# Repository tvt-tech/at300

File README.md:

# AT300 serial control tool for RP2040 (Micropython)

## Flashing (using [uv](https://docs.astral.sh/uv/getting-started/))
```shell
git clone https://github.com/tvt-tech/at300
cd at300
uv run -s flash.py -p /dev/ttyUSB0 -b 115200
```

## Upgrade
```shell
git pull
uv run -s flash.py -p /dev/ttyUSB0 -b 115200
```

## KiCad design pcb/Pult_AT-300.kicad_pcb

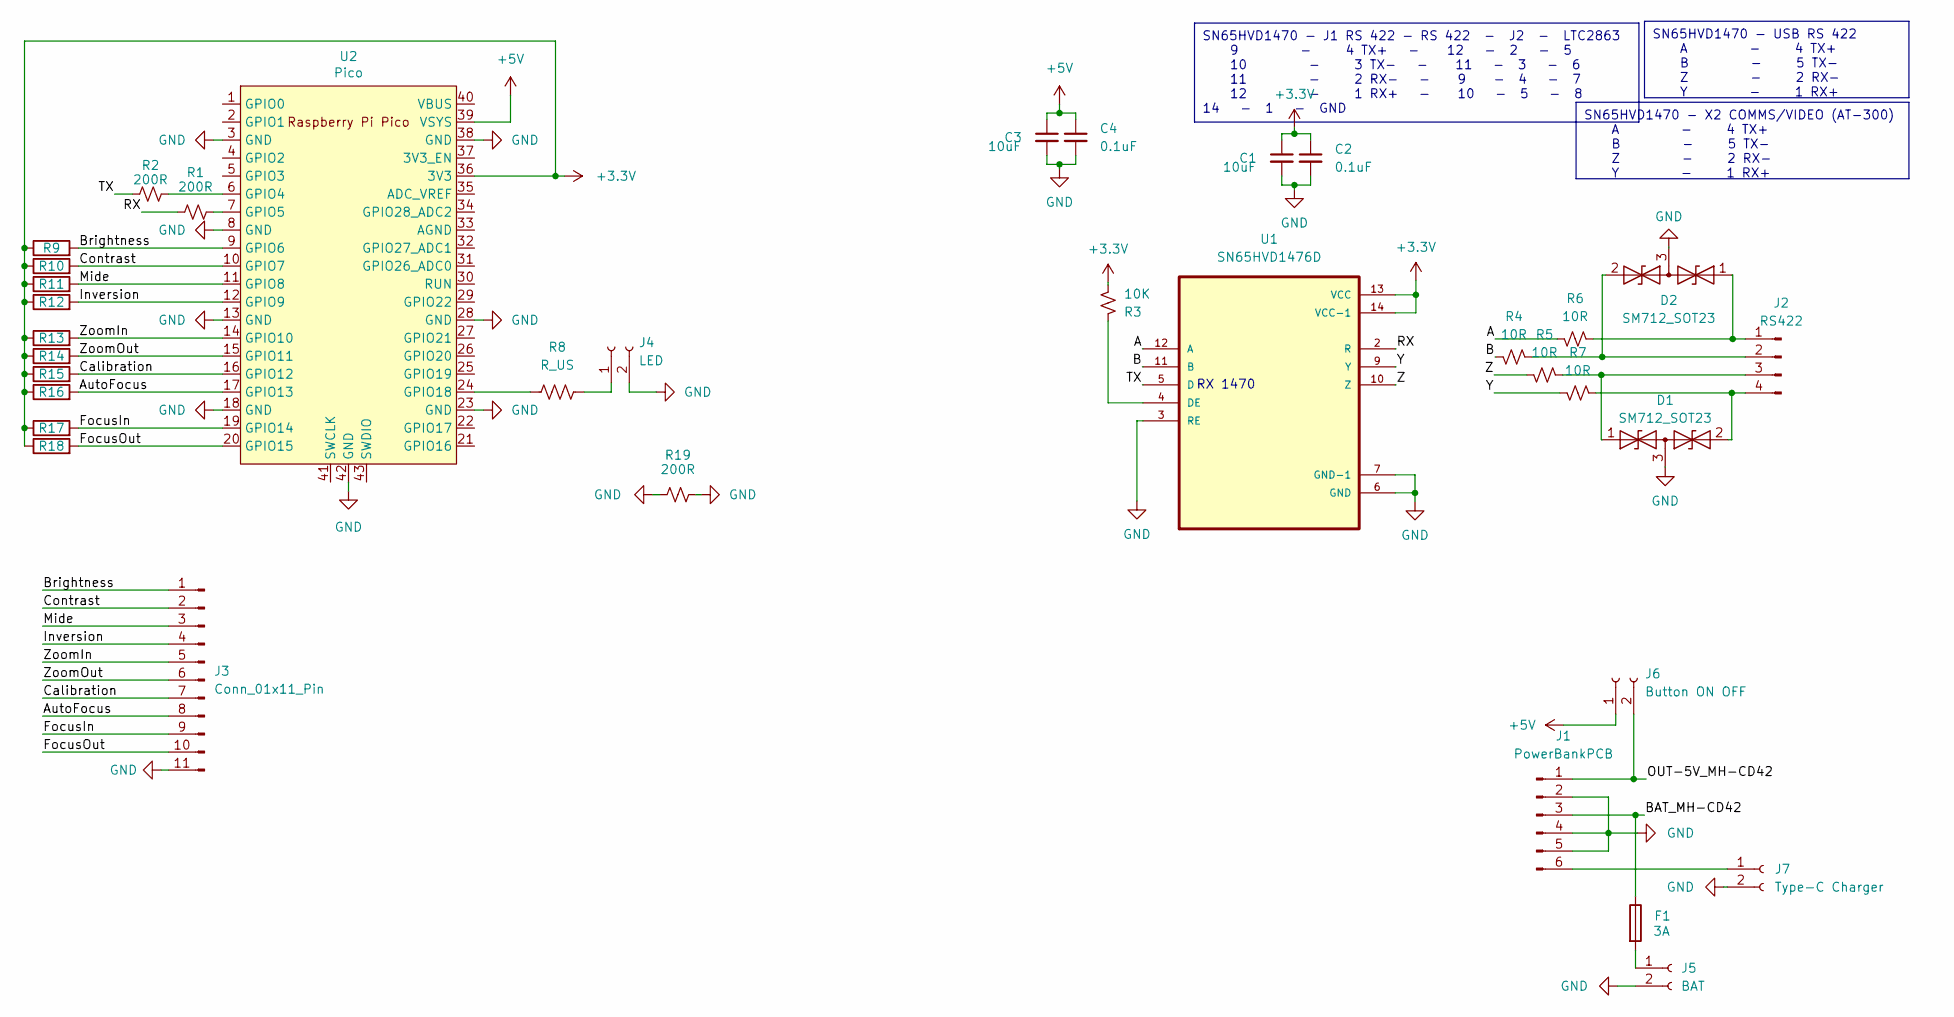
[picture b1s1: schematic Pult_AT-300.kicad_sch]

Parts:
C1, C3: 10uF; C_1206_3216Metric
C2, C4: 0.1uF; C_0603_1608Metric
D1, D2: SM712_SOT23; SOT-23
F1: 3А; R_1812_4532Metric
J1: PowerBankPCB; PinHeader_1x06_P2.54mm_Vertical
J2: RS422; PinSocket_1x04_P2.54mm_Vertical
J3: Conn_01x11_Pin; PinHeader_1x11_P2.54mm_Vertical
J4: LED; PinHeader_1x02_P2.54mm_Vertical
J5: BAT; PinHeader_1x02_P2.54mm_Vertical
J6: Button ON OFF; TerminalBlock_MetzConnect_Type011_RT05502HBWC_1x02_P5.00mm_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
J7: Type-C Charger; PinHeader_1x02_P2.54mm_Vertical
R1, R2: 200R; R_0603_1608Metric
R3: 10K; R_0603_1608Metric
R4, R5, R6, R7: 10R; R_0603_1608Metric
R8: R_US; R_0603_1608Metric
R9, R10, R11, R12, R13, R14, R15, R16, R17, R18: R; R_0603_1608Metric
R19: 200R; R_1206_3216Metric
U1: SN65HVD1476D; SOIC-14_3.9x8.7mm_P1.27mm
U2: Pico; RPi_Pico_SMD_TH

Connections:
+3.3V: C1.1, C2.1, R3.1, R9.1, R10.1, R11.1, R12.1, R13.1, R14.1, R15.1, R16.1, R17.1, R18.1, U1.13 (VCC), U1.14 (VCC-1), U2.36 (3V3)
+5V: C3.1, C4.1, J6.1, U2.39 (VSYS)
/A: R6.2, U1.12 (A)
/AutoFocus: J3.8, R16.2, U2.17 (GPIO13)
/B: R4.2, U1.11 (B)
/BAT_MH-CD42: F1.1, J1.3
/Brightness: J3.1, R9.2, U2.9 (GPIO6)
/Calibration: J3.7, R15.2, U2.16 (GPIO12)
/Contrast: J3.2, R10.2, U2.10 (GPIO7)
/FocusIn: J3.9, R17.2, U2.19 (GPIO14)
/FocusOut: J3.10, R18.2, U2.20 (GPIO15)
/Inversion: J3.4, R12.2, U2.12 (GPIO9)
/Mide: J3.3, R11.2, U2.11 (GPIO8)
/OUT-5V_MH-CD42: J1.1, J6.2
/RX: R1.1, U1.2 (R)
/TX: R2.1, U1.5 (D)
/Y: R7.2, U1.9 (Y)
/Z: R5.2, U1.10 (Z)
/ZoomIn: J3.5, R13.2, U2.14 (GPIO10)
/ZoomOut: J3.6, R14.2, U2.15 (GPIO11)
GND: C1.2, C2.2, C3.2, C4.2, D1.3 (common), D2.3 (common), J1.2, J1.4, J1.5, J3.11, J4.2, J5.2, J7.2, R19.1, R19.2, U1.3 (RE), U1.6 (GND), U1.7 (GND-1), U2.3 (GND), U2.8 (GND), U2.13 (GND), U2.18 (GND), U2.23 (GND), U2.28 (GND), U2.38 (GND), U2.42 (GND)
unnamed: D1.1 (A1), J2.3, R5.1
unnamed: D1.2 (A2), J2.4, R7.1
unnamed: D2.1 (A1), J2.1, R6.1
unnamed: D2.2 (A2), J2.2, R4.1
unnamed: J1.6, J7.1
unnamed: J4.1, R8.2
unnamed: F1.2, J5.1
unnamed: R3.2, U1.4 (DE)
unnamed: R2.2, U2.6 (GPIO4)
unnamed: R1.2, U2.7 (GPIO5)
unnamed: R8.1, U2.24 (GPIO18)

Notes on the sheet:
SN65HVD1470 - J1 RS 422 - RS 422 - J2 - LTC2863 9 - 4 TX+ - 12 - 2 - 5 10 - 3 TX- - 11 - 3 - 6 11 - 2 RX- - 9 - 4 - 7 12 - 1 RX+ - 10 - 5 - 8 14 - 1 - GND
SN65HVD1470 - X2 COMMS/VIDEO (AT-300) A - 4 TX+ B - 5 TX- Z - 2 RX- Y - 1 RX+
SN65HVD1470 - USB RS 422 A - 4 TX+ B - 5 TX- Z - 2 RX- Y - 1 RX+
RX 1470

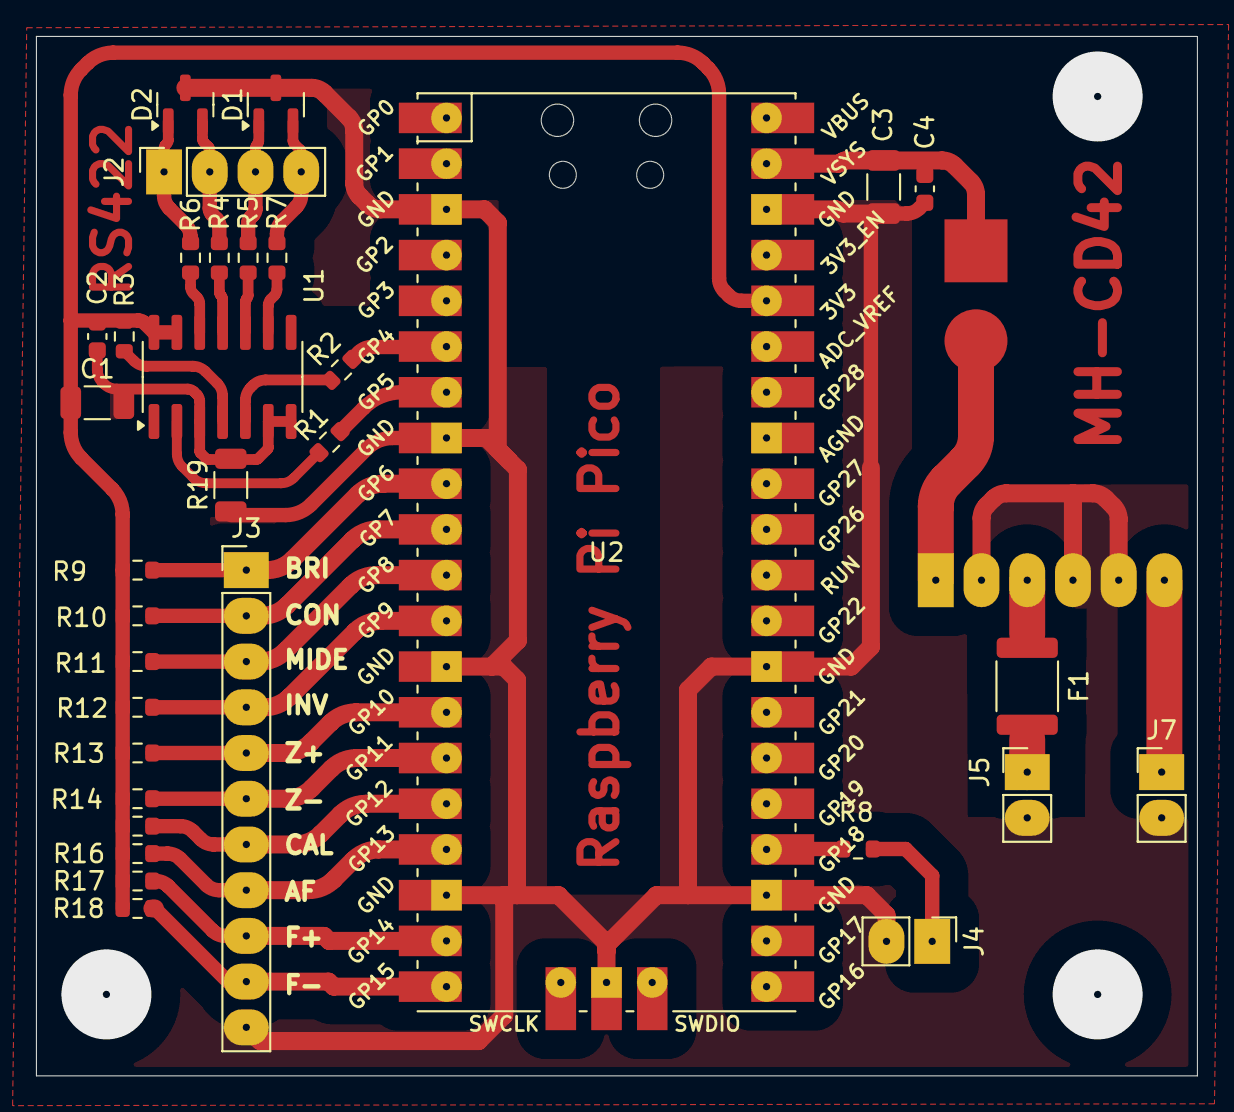
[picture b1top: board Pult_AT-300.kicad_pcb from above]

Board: 2 copper layers, 64.5 x 57.7 mm, 35 parts (1 on the bottom side), 32 nets.

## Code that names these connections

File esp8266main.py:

import time

from machine import UART, Pin

import api

LED = Pin(25, Pin.OUT)

uart = UART(1, baudrate=115200, stop=2)
# RS422Pin = Pin(2, Pin.OUT)
# RS422Pin.on()


class Status:
    Brightness = len(api.CONTRAST) - 1
    Contrast = len(api.BRIGHTNESS) - 1
    Mide = len(api.MIDE) - 1
    Zoom = len(api.Zoom) - 1
    Inversion = api.WhiteHot


# class Button:
#     Brightness = Pin(6, Pin.IN, Pin.PULL_UP)
#     Contrast = Pin(7, Pin.IN, Pin.PULL_UP)
#     Mide = Pin(8, Pin.IN, Pin.PULL_UP)
#     Inversion = Pin(9, Pin.IN, Pin.PULL_UP)
#
#     ZoomIn = Pin(10, Pin.IN, Pin.PULL_UP)
#     ZoomOut = Pin(11, Pin.IN, Pin.PULL_UP)
#     Calibration = Pin(12, Pin.IN, Pin.PULL_UP)
#     AutoFocus = Pin(13, Pin.IN, Pin.PULL_UP)
#
#     FocusIn = Pin(14, Pin.IN, Pin.PULL_UP)
#     FocusOut = Pin(15, Pin.IN, Pin.PULL_UP)


# class ButtonState:
#     Brightness = 0
#     Contrast = 0
#     Mide = 0
#     Inversion = 0
#     AutoFocus = 0
#     ZoomIn = 0
#     ZoomOut = 0
#     Calibration = 0
#     FocusIn = 0
#     FocusOut = 0
#     FocusStop = 1


def send_command(command: list[int]):
    ret = uart.write(bytes(command))
    print(f"UART: bytes sent: {ret}")


# def handle_contrast_btn():
#     if Button.Contrast.value():
#         ButtonState.Contrast = 0
#     elif ButtonState.Contrast != 1:
#         ButtonState.Contrast = 1
#         Status.Contrast += 1
#         if Status.Contrast == len(api.CONTRAST):
#             Status.Contrast = 0
#         send_command(api.CONTRAST[Status.Contrast])
#         print(f"{Status.Contrast=}")
#
#
# def handle_brightness_btn():
#     if Button.Brightness.value():
#         ButtonState.Brightness = 0
#     elif ButtonState.Brightness != 1:
#         ButtonState.Brightness = 1
#         Status.Brightness += 1
#         if Status.Brightness == len(api.BRIGHTNESS):
#             Status.Brightness = 0
#         send_command(api.BRIGHTNESS[Status.Brightness])
#         print(f"{Status.Brightness=}")
#
#
# def handle_mide_btn():
#     if Button.Mide.value():
#         ButtonState.Mide = 0
#     elif ButtonState.Mide != 1:
#         ButtonState.Mide = 1
#         Status.Mide += 1
#         if Status.Mide == len(api.MIDE):
#             Status.Mide = 0
#         send_command(api.MIDE[Status.Mide])
#         print(f"{Status.Mide=}")
#
#
# def handle_zoomin_btn():
#     if Button.ZoomIn.value():
#         ButtonState.ZoomIn = 0
#     elif ButtonState.ZoomIn != 1:
#         ButtonState.ZoomIn = 1
#         if Status.Zoom + 1 < len(api.Zoom):
#             Status.Zoom += 1
#             send_command(api.Zoom[Status.Zoom])
#         print(f"{Status.Zoom=}")
#
#
# def handle_zoomout_btn():
#     if Button.ZoomOut.value():
#         ButtonState.ZoomOut = 0
#     elif ButtonState.ZoomOut != 1:
#         ButtonState.ZoomOut = 1
#         if Status.Zoom > 0:
#             Status.Zoom -= 1
#             send_command(api.Zoom[Status.Zoom])
#         print(f"{Status.Zoom=}")
#
#
# def handle_calibration_btn():
#     if Button.Calibration.value():
#         ButtonState.Calibration = 0
#     elif ButtonState.Calibration != 1:
#         ButtonState.Calibration = 1
#         send_command(api.Calibration)
#         print("Calibration")
#
#
# def handle_autofocus_btn():
#     if Button.AutoFocus.value():
#         ButtonState.AutoFocus = 0
#     elif ButtonState.AutoFocus != 1:
#         ButtonState.AutoFocus = 1
#         send_command(api.AutoFocus)
#         print("AutoFocus")
#
#
# def handle_focusin_btn():
#     if Button.FocusIn.value():
#         ButtonState.FocusIn = 0
#     elif ButtonState.FocusIn != 1:
#         ButtonState.FocusIn = 1
#         send_command(api.FocusIn)
#         print("FocusIn")
#
#
# def handle_focusout_btn():
#     if Button.FocusOut.value():
#         ButtonState.FocusOut = 0
#     elif ButtonState.FocusOut != 1:
#         ButtonState.FocusOut = 1
#         send_command(api.FocusOut)
#         print("FocusOut")
#
#
# def handle_foucusstop():
#     if Button.FocusOut.value() and Button.FocusIn.value():
#         if ButtonState.FocusStop == 0:
#             ButtonState.FocusStop = 1
#             send_command(api.FocusStop)
#             print("FocusStop")
#     elif ButtonState.FocusStop == 1:
#         ButtonState.FocusStop = 0
#
#
# def handle_inversion_btn():
#     if Button.Inversion.value():
#         ButtonState.Inversion = 0
#     elif ButtonState.Inversion != 1:
#         ButtonState.Inversion = 1
#         if Status.Inversion == api.WhiteHot:
#             send_command(api.BlackHot)
#             Status.Inversion = api.BlackHot
#         else:
#             send_command(api.WhiteHot)
#             Status.Inversion = api.WhiteHot
#         print(f"{Status.Inversion=}")


def inversion_switch():
    time.sleep_ms(5000)
    if Status.Inversion == api.WhiteHot:
        send_command(api.BlackHot)
        Status.Inversion = api.BlackHot
    else:
        send_command(api.WhiteHot)
        Status.Inversion = api.WhiteHot
    print(f"{Status.Inversion=}")


def init():
    ...


def main():

    timer = 5000

    while True:
        time.sleep_ms(100)
        timer -= 100
        if timer <= 0:
            LED.value(int(not LED.value()))
            inversion_switch()
            timer = 5000

        # handle_brightness_btn()
        # handle_contrast_btn()
        # handle_mide_btn()
        #
        # handle_zoomin_btn()
        # handle_zoomout_btn()
        #
        # handle_autofocus_btn()
        # handle_focusin_btn()
        # handle_focusout_btn()
        # handle_foucusstop()
        #
        # handle_calibration_btn()
        # handle_inversion_btn()



main()

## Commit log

2024-04-24 initial
2024-04-30 Index error fix
2024-04-30 focus implemented
2024-05-07 update crc_ccitt
2024-05-07 update Calibration crc
2024-05-15 zoom command compile
2024-05-15 polarity fix
2024-05-15 add periodic status check
2024-05-15 remove periodic status check
2024-05-20 fix zoom order
2024-06-07 try-new-calibration
2024-06-11 calibration fix
2025-04-23 23.04.25
2025-04-23 23.04.25 + ping
2025-04-23 23.04.25 + flash.py + uv compatibility
2025-04-23 added pcb
